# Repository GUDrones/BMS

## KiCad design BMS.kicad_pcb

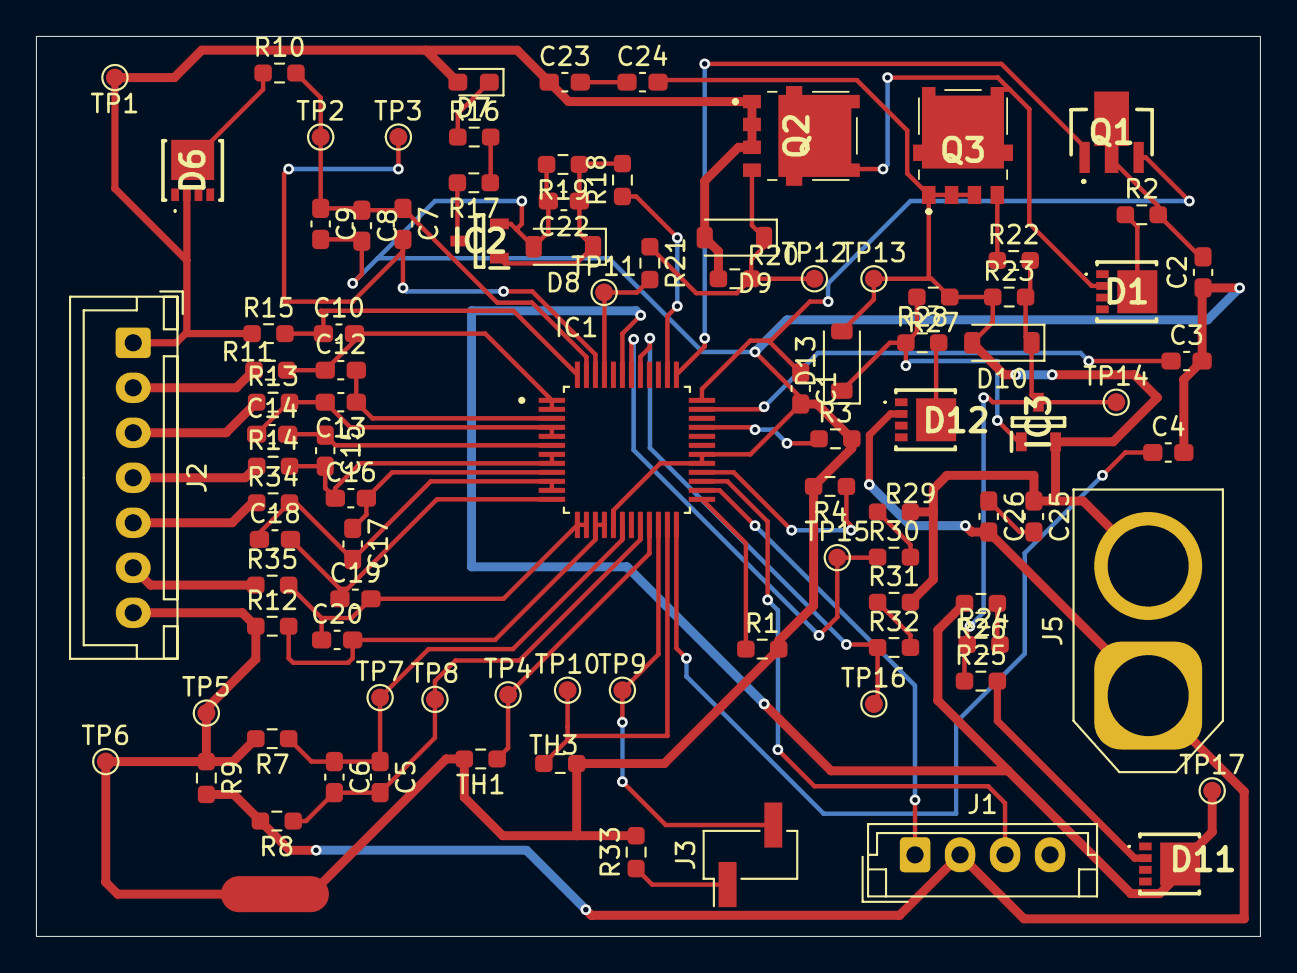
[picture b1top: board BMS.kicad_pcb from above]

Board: 2 copper layers, 68.0 x 50.0 mm, 96 parts (0 on the bottom side), 62 nets.

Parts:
C1: 22nF; C_0603_1608Metric_Pad1.08x0.95mm_HandSolder
C2, C3, C8, C9: 1uF; C_0603_1608Metric_Pad1.08x0.95mm_HandSolder
C4: 2.2uF; C_0603_1608Metric_Pad1.08x0.95mm_HandSolder
C5: 100pF; C_0603_1608Metric_Pad1.08x0.95mm_HandSolder
C6, C22, C23, C24, C25, C26: 0.1uF; C_0603_1608Metric_Pad1.08x0.95mm_HandSolder
C7: 0.47uF; C_0603_1608Metric_Pad1.08x0.95mm_HandSolder
C10, C12, C13, C14, C15, C16, C17, C18, C19, C20: 220nF; C_0603_1608Metric_Pad1.08x0.95mm_HandSolder
D1, D6, D11, D12: 100V; V5N3M153M3I
D7: LED; LED_0603_1608Metric_Pad1.05x0.95mm_HandSolder
D8: 10V; D_SOD-123
D9, D10, D13: 16V; D_SOD-123
IC1: BQ7695201PFBR; QFP50P900X900X120-48N
IC2, IC3: PMV213SN,215; SOT95P230X110-3N
J1: Conn_01x04_Pin; JST_EH_B4B-EH-A_1x04_P2.50mm_Vertical
J2: Conn_01x07_Pin; JST_XH_B7B-XH-A_1x07_P2.50mm_Vertical
J3: Conn_01x02_Pin; PinHeader_1x02_P2.54mm_Vertical_SMD_Pin1Left
J5: Conn_01x02_Pin; AMASS_XT60-M_1x02_P7.20mm_Vertical
NT1: NetTie_2; NetTie-2_SMD_Pad2.0mm
Q1: FCX495TA; FCX495QTA
Q2, Q3: NTMFS5C628NLT1G; NTMFS5C460NLT1G
R1, R3, R4: 1.0k; R_0603_1608Metric_Pad0.98x0.95mm_HandSolder
R2: 300; R_0603_1608Metric_Pad0.98x0.95mm_HandSolder
R7, R8, R10: 100; R_0603_1608Metric_Pad0.98x0.95mm_HandSolder
R9: 0.001; R_0603_1608Metric_Pad0.98x0.95mm_HandSolder
R11, R12, R13, R14, R15, R34, R35: 20; R_0603_1608Metric_Pad0.98x0.95mm_HandSolder
R16, R17: 7.5k; R_0603_1608Metric_Pad0.98x0.95mm_HandSolder
R18, R21, R24, R26, R29, R30, R31, R32: 5.1k; R_0603_1608Metric_Pad0.98x0.95mm_HandSolder
R19: 20k; R_0603_1608Metric_Pad0.98x0.95mm_HandSolder
R20, R23, R27: 10M; R_0603_1608Metric_Pad0.98x0.95mm_HandSolder
R22: 0; R_0603_1608Metric_Pad0.98x0.95mm_HandSolder
R25: 7.50k; R_0603_1608Metric_Pad0.98x0.95mm_HandSolder
R28, R33: 10k; R_0603_1608Metric_Pad0.98x0.95mm_HandSolder
TH1, TH3: Thermistor; R_0603_1608Metric_Pad0.98x0.95mm_HandSolder
TP1: BAT+; TestPoint_Pad_D1.0mm
TP2: BAT; TestPoint_Pad_D1.0mm
TP3, TP4, TP5, TP10, TP11, TP12, TP13, TP14, TP17: TestPoint_Pad_D1.0mm
TP6: BAT-; TestPoint_Pad_D1.0mm
TP7: SRP; TestPoint_Pad_D1.0mm
TP8: SRN; TestPoint_Pad_D1.0mm
TP9: TS2; TestPoint_Pad_D1.0mm
TP15: PACK; TestPoint_Pad_D1.0mm
TP16: LD; TestPoint_Pad_D1.0mm

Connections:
6P: C23.1, D6.2 (A), D7.2 (A), D9.2 (A), J2.1, Q2.1, Q2.2, Q2.3, R15.1, R20.1, TP1.1
BAT-: J2.7, NT1.1, R7.2, R9.1, R12.1, TP5.1, TP6.1
CD: D1.2 (A), Q2.5, Q3.5
CHG: IC1.45 (CHG), R21.2, TP11.1
DSG: D11.5 (K), IC1.43 (DSG), R26.2, TP17.1
FUSE: IC1.38 (FUSE), R18.1
GND: C1.2, C2.1, C3.2, C4.2, C8.2, C9.2, C22.2, D8.2 (A), IC1.17 (VSS), IC1.29 (CFETOFF), IC1.30 (DFETOFF), IC2.2 (S), NT1.2, R1.2, R3.2, R4.2, R19.2, R33.2, TH1.2, TH3.2
LD: IC1.41 (LD), R32.1, TP16.1
unnamed: C23.2, C24.1
unnamed: C25.2, C26.1
unnamed: D1.5 (K), R2.1
unnamed: D6.5 (K), R10.1
unnamed: D7.1 (K), R16.1
unnamed: C22.1, D8.1 (K), IC2.1 (G), R18.2, R19.1
unnamed: D9.1 (K), Q2.4, R20.2, R21.1, TP12.1
unnamed: C24.2, C25.1, D10.2 (A), D13.2 (A), IC3.2 (S), J5.2, Q3.1, Q3.2, Q3.3, R23.1, R27.1, R29.2, R31.2, TP13.1
unnamed: D10.1 (K), IC3.3 (D), R22.2, R23.2, R24.1, R25.1, TP14.1
unnamed: D11.2 (A), R25.2
unnamed: D12.5 (K), R28.2
unnamed: D13.1 (K), IC3.1 (G), R27.2, R28.1
unnamed: IC1.25 (ALERT), R1.1
unnamed: C7.1, C8.1, C9.1, IC1.47 (BAT), R10.2, TP2.1
unnamed: IC1.37 (BREG), Q1.1 (B)
unnamed: C7.2, IC1.46 (CP1), TP3.1
unnamed: IC1.28 (HDQ), R4.1
unnamed: C3.1, IC1.35 (REG1)
unnamed: C4.1, IC1.24 (REG18)
unnamed: C1.1, IC1.36 (REGIN), Q1.3 (E)
unnamed: IC1.33 (RST_SHUT), R3.1
unnamed: IC1.26 (SCL), J1.1
unnamed: IC1.27 (SDA), J1.3
unnamed: C5.2, C6.2, IC1.20 (SRN), R8.1, TP8.1
unnamed: C5.1, C6.1, IC1.18 (SRP), R7.1, TP7.1
unnamed: IC1.21 (TS1), TH1.1, TP4.1
unnamed: IC1.22 (TS2), J3.2, TP9.1
unnamed: IC1.23 (TS3), TH3.1, TP10.1
unnamed: C20.2, IC1.15 (VC1), IC1.16 (VC0), R12.2
unnamed: C19.2, C20.1, IC1.13 (VC3), IC1.14 (VC2), R35.2
unnamed: C18.2, C19.1, IC1.12 (VC4)
unnamed: C17.2, C18.1, IC1.10 (VC6), IC1.11 (VC5), R34.2
unnamed: C16.2, C17.1, IC1.9 (VC7)
unnamed: C15.2, C16.1, IC1.7 (VC9), IC1.8 (VC8), R14.2
unnamed: C14.2, C15.1, IC1.6 (VC10)
unnamed: C13.2, C14.1, IC1.4 (VC12), IC1.5 (VC11), R13.2
unnamed: C12.2, C13.1, IC1.3 (VC13)
unnamed: C10.2, C12.1, IC1.1 (VC15), IC1.2 (VC14), R11.2
unnamed: C10.1, IC1.48 (VC16), R15.2
unnamed: IC2.3 (D), R17.2
unnamed: J2.2, R11.1
unnamed: J2.3, R13.1
unnamed: J2.4, R14.1
unnamed: J2.5, R34.1
unnamed: J2.6, R35.1
unnamed: J3.1, R33.1
unnamed: C2.2, Q1.2 (C_1), Q1.4 (C_2), R2.2
unnamed: Q3.4, R22.1
unnamed: R16.2, R17.1
unnamed: R24.2, R26.1
unnamed: R29.1, R30.2
unnamed: R31.1, R32.2
PACK: IC1.42 (PACK), R30.1, TP15.1
PGND: C26.2, D12.2 (A), J1.2, J5.1, R8.2, R9.2

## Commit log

2025-02-20 Zabis BMS research
2025-04-07 updated the schematic and uploaded the pcb file
